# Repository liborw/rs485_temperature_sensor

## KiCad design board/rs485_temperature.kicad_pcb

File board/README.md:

## Calculations

 - DC/DC Buck [L6981](L6981.md)

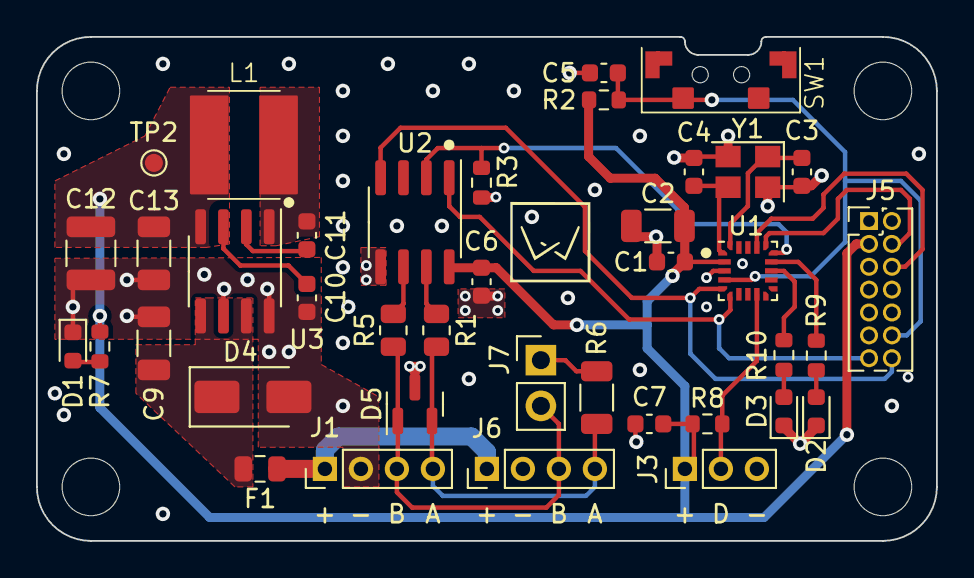
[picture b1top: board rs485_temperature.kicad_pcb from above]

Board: 4 copper layers, 50.0 x 28.0 mm, 44 parts (0 on the bottom side), 26 nets.

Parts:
C1, C7, C11: 100nF; C_0603_1608Metric
C2: 4.7uF; C_1206_3216Metric
C3, C4, C5: C_Small; C_0603_1608Metric
C6: 4.7uF; C_0603_1608Metric
C9, C13: 10uF; C_1206_3216Metric
C10: 1uF; C_0603_1608Metric
C12: 22uF; C_1210_3225Metric
D1, D2: RED; LED_0603_1608Metric
D3: GREEN; LED_0603_1608Metric
D4: 40V; D_SMA
D5: SM712; SOT-23
F1: 100mA; Fuse_0805_2012Metric
G1: LiborW_neg_10x10; LiborW_neg_5x5
H1, H2, H3, H4: M3; MountingHole_3.2mm_M3_ISO7380
J1: RS485_IN; PinHeader_1x04_P2.00mm_Vertical
J3: DS18S20; PinHeader_1x03_P2.00mm_Vertical
J5: STDC14; PinHeader_2x07_P1.27mm_Vertical
J6: RS485_OUT; PinHeader_1x04_P2.00mm_Vertical
J7: RS485 TERM; PinHeader_1x02_P2.54mm_Vertical
L1: 56uH; L_Ferrocore_DLG-0504
R1, R5: 10k; R_0805_2012Metric
R2: 10k; R_0603_1608Metric
R3: 4k7; R_0603_1608Metric
R6: 120R; R_1206_3216Metric
R7, R9, R10: 1k; R_0603_1608Metric
R8: 120R; R_0603_1608Metric
SW1: SW_Push; Push_Button_G71Y_3X6X3.5MM
TP2: TestPoint; TestPoint_Pad_D1.0mm
U1: STM32C011F6Ux; ST_UFQFPN-20_3x3mm_P0.5mm
U2: THVD1400D; SOIC-8_3.9x4.9mm_P1.27mm
U3: L6981N33DR; SOIC-8_3.9x4.9mm_P1.27mm
Y1: 48MHz; Crystal_SMD_3225-4Pin_3.2x2.5mm

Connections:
+3V3: C1.1, C2.1, C6.1, C7.1, C12.2, C13.2, J3.1, J5.3 (VCC), L1.2, R2.1, R7.1, R8.1, TP2.1, U1.2 (VDD), U2.8 (VCC), U3.4 (VOUT/FB)
+24V: C9.2, D4.1 (K), F1.2, U3.5 (EN/CLKIN), U3.7 (VIN)
/MCU (STMC011F6Ux)/DEBUG_SWCLK: J5.6 (JCLK/SWCLK), U1.17 (PA14)
/MCU (STMC011F6Ux)/DEBUG_SWDIO: J5.4 (JTMS/SWDIO), U1.16 (PA13)
/MCU (STMC011F6Ux)/DQ: J3.2, R8.2, U1.9 (PA4)
/MCU (STMC011F6Ux)/LED_S1: R9.1, U1.14 (PA9/PA11)
/MCU (STMC011F6Ux)/LED_S2: R10.1, U1.13 (PA8)
/MCU (STMC011F6Ux)/RCC_OSCX_IN: C3.1, U1.20 (PC14), Y1.1
/MCU (STMC011F6Ux)/RCC_OSCX_OUT: C4.1, U1.1 (PC15), Y1.3
/MCU (STMC011F6Ux)/USART1_DE: R3.1, U1.15 (PA10/PA12), U2.2 (~RE), U2.3 (DE)
/MCU (STMC011F6Ux)/USART1_RX: J5.13 (VCP_RX), U1.6 (PA1), U2.1 (RO)
/MCU (STMC011F6Ux)/USART1_TX: J5.14 (VCP_TX), U1.5 (PA0), U2.4 (DI)
/MCU (STMC011F6Ux)/~RST: C5.1, J5.12 (~RST), R2.2, SW1.1, U1.4 (PF2)
/POWER (L6981)/BOOT: C11.1, U3.2 (BOOT)
/POWER (L6981)/SW: C11.2, L1.1, U3.1 (SW)
/POWER (L6981)/VCC: C10.2, U3.3 (VCC)
/PWR: F1.1, J1.1, J6.1
/RS485 (THVD1400D)/RS485_A: D5.2 (A2), J1.4, J6.4, R1.2, R6.1
/RS485 (THVD1400D)/RS485_B: D5.1 (A1), J1.3, J6.3, J7.2, R5.2
GND: C1.2, C2.2, C3.2, C4.2, C5.2, C6.2, C7.2, C9.1, C10.1, C12.1, C13.1, D1.1 (K), D2.1 (K), D3.1 (K), D4.2 (A), D5.3 (common), J1.2, J3.3, J5.5 (GND), J5.7 (GND), J5.11 (GNDDetect), J6.2, R3.2, SW1.2, U1.3 (VSS), U2.5 (GND), U3.6 (AGND), U3.8 (PGND), Y1.2, Y1.4
unnamed: D1.2 (A), R7.2
unnamed: D2.2 (A), R9.2
unnamed: D3.2 (A), R10.2
unnamed: J7.1, R6.2
unnamed: R5.1, U2.6 (A)
unnamed: R1.1, U2.7 (B)

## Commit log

2023-07-19 Initial commit WIP
2023-07-20 Final update
2023-07-26 Update board
2023-07-26 Add build script and fig dir
2023-07-26 Add 3d renders
